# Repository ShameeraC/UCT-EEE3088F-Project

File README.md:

# EEE3088F Group 18 Sensing HAT (Version 1.0)
This project is a group project for the course EEE3088F at UCT. The purpose of the HAT is to detect light and move a motor or another device in the direction of the light.

# Instructions For Use (For Version 1.0)
    
    - Hardware Requirements - 

    To use this HAT, a mini-USB connector is required to interface the HAT with the STM 
    (Or whatever other microcontroller is in use). That being said, an STM32F0 discovery board, 
    or another board containing a microcontroller with read/write/ADC/memory capabilities must be used if 
    the full functionality of the HAT is to be claimed.
    The USB must be capable of data transmission.
    A 5V Li-Ion battery and battery holder are necessary for the powering of the HAT, unless some other 
    power source is to be used. Jumper cables are necessary for the current design, as it does not conform
    to the general standard of board measurements (they are needed to connect the HAT to the board in use).
   
    - Software Requirements -

    The coding of this board can be done via the STM Cube IDE (preferred) or Code Blocks. Other coding
    platforms can work as well. The terminal must be configured to drive the USB ports that connect to the
    discovery board or the HAT. 
    Programs can be uploaded to the STM or to the HAT itself, depending on which method is preferred.
    The EEPROM on the HAT must be coded via the HAT's USB port, as this sends data to and from the FTDI
    and the EEPROM on board the HAT together. 
    Currently the HAT has not been revised, and secondary versions have not yet been created. Because of this,
    the recommended approach to coding is to do so via the STM or the board in use (and not via the HAT).
    The temperature sensor which sends data to and from the HAT's EEPROM was not populated in version 1.0,
    and as such the EEPROM and the FTDI on board the HAT are not needed or useful currently.
    Thus, any code that is written should be uploaded directly to the board in use, after which wiring
    can interface the board with the HAT.

    - Initialization Instructions -

    To initialize the hardware, connect the battery to the HAT to power the STM board (if batteries 
    are not being used, find another way to connect the HAT to power). Connect each 
    pin on the STM to the corresponding pin on the HAT via jumper wires.
    To initialize the software, connect to the board via a USB, and compile and upload the desired 
    code to the board via an appropriate IDE. How to upload code to the board will vary from IDE to
    IDE. Check the IDE's online documentation for further details.

    - Running Your First Program on the HAT - 

    To run your first program on the HAT, refer to the self-explanatory code in the "main.c" file
    in the following directory:
    "Firmware/GROUP18 Microcontroler Interfacing/Core/src/main.c"
    This file can be run to toggle two user connected LEDs based on the strength of light sensed by
    the LDRs on the HAT. To set up the hardware for this basic program, two LEDs should be connected
    in series with 1k resistors which will be connected to GPIOA and GPIOB on the STM (GPIO pin 10 and
    pin 12 respectively). Alternitavely, the LEDs on the STM can be flashed based on the state of the
    LDRs if the STM LEDs are set to "HIGH" in the lightSensingInit() function (this would need to be
    added). Inside of the while loop in the code, the first statement is a call to initialize the light
    sensing sequence, and so everything is set up for ease of use.
    Have fun!! 

# Directories:
This repo has the following subfolders, which provide a useful common structure for custom electronics projects: \
    * Documentation: Project documentation (including submissions) and component datasheets are stored here.\
    * Firmware: Any software developed for the hat will be stored here.\
    * PCB: This includes all KiCad files (schematics, pcb, gerber files, footprints etc.). The main KiCad folder is here. \
    * Production: The gerber files, BOM, Budget, or anything required by JLCPCB will be stored here. \
    * Simulation: Any simulation files (eg SPICE) or design stage generated results (Eg matlab or excel) will be stored here.

# PCB Designers:
JONATHAN APPS \
SHAMEERA CASSIM \
JAHAR PERSAD 

# License
[Creative Commons Attribution 4.0 International license](https://choosealicense.com/licenses/cc-by-4.0/)

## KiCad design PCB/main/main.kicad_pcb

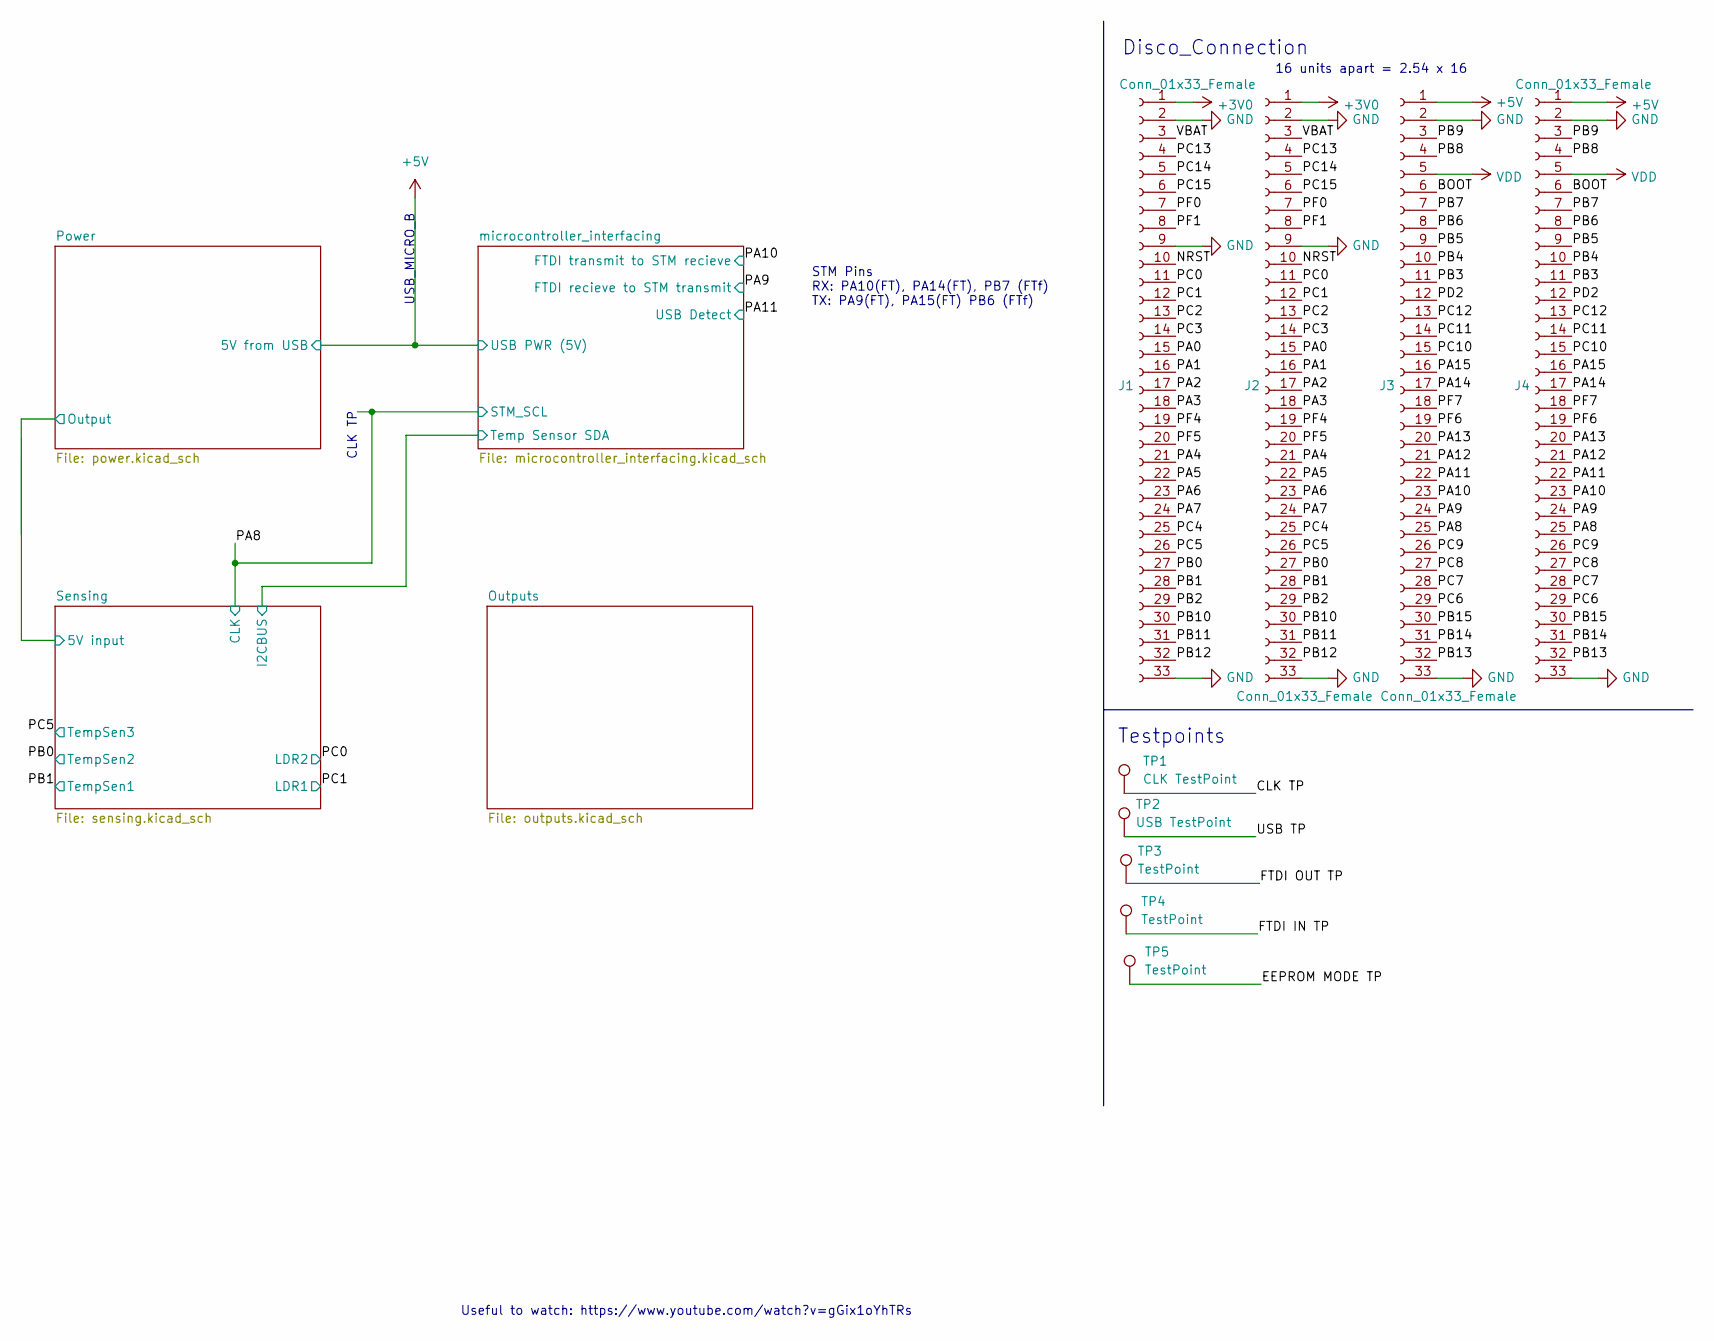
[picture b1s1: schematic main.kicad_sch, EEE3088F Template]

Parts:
J1, J4: Conn_01x33_Female; PinHeader_1x33_P2.54mm_Vertical
J2, J3: Conn_01x33_Female; PinSocket_1x33_P2.54mm_Vertical
TP1: CLK TestPoint; TestPoint_2Pads_Pitch2.54mm_Drill0.8mm
TP2: USB TestPoint; TestPoint_2Pads_Pitch2.54mm_Drill0.8mm
TP3, TP4, TP5: TestPoint; TestPoint_2Pads_Pitch2.54mm_Drill0.8mm

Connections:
+3V0: J1.1, J2.1
+5V: J3.1, J4.1; also elsewhere on the board
/BOOT: J3.6, J4.6
/NRST: J1.10, J2.10
/PA0: J1.15, J2.15
/PA1: J1.16, J2.16
/PA2: J1.17, J2.17
/PA3: J1.18, J2.18
/PA4: J1.21, J2.21
/PA5: J1.22, J2.22
/PA6: J1.23, J2.23
/PA7: J1.24, J2.24
/PA8: J3.25, J4.25; also elsewhere on the board
/PA9: J3.24, J4.24; also elsewhere on the board
/PA10: J3.23, J4.23; also elsewhere on the board
/PA11: J3.22, J4.22; also elsewhere on the board
/PA12: J3.21, J4.21
/PA13: J3.20, J4.20
/PA14: J3.17, J4.17
/PA15: J3.16, J4.16
/PB0: J1.27, J2.27; also elsewhere on the board
/PB1: J1.28, J2.28; also elsewhere on the board
/PB2: J1.29, J2.29
/PB3: J3.11, J4.11
/PB4: J3.10, J4.10
/PB5: J3.9, J4.9
/PB6: J3.8, J4.8
/PB7: J3.7, J4.7
/PB8: J3.4, J4.4
/PB9: J3.3, J4.3
/PB10: J1.30, J2.30
/PB11: J1.31, J2.31
/PB12: J1.32, J2.32
/PB13: J3.32, J4.32
/PB14: J3.31, J4.31
/PB15: J3.30, J4.30
/PC0: J1.11, J2.11; also elsewhere on the board
/PC1: J1.12, J2.12; also elsewhere on the board
/PC2: J1.13, J2.13
/PC3: J1.14, J2.14
/PC4: J1.25, J2.25
/PC5: J1.26, J2.26; also elsewhere on the board
/PC6: J3.29, J4.29
/PC7: J3.28, J4.28
/PC8: J3.27, J4.27
/PC9: J3.26, J4.26
/PC10: J3.15, J4.15
/PC11: J3.14, J4.14
/PC12: J3.13, J4.13
/PC13: J1.4, J2.4
/PC14: J1.5, J2.5
/PC15: J1.6, J2.6
/PD2: J3.12, J4.12
/PF0: J1.7, J2.7
/PF1: J1.8, J2.8
/PF4: J1.19, J2.19
/PF5: J1.20, J2.20
/PF6: J3.19, J4.19
/PF7: J3.18, J4.18
/VBAT: J1.3, J2.3
GND: J1.2, J1.9, J1.33, J2.2, J2.9, J2.33, J3.2, J3.33, J4.2, J4.33; also elsewhere on the board
VDD: J3.5, J4.5

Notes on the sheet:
Useful to watch: https://www.youtube.com/watch?v=gGix1oYhTRs
CLK TP
STM Pins RX: PA10(FT), PA14(FT), PB7 (FTf) TX: PA9(FT), PA15(FT) PB6 (FTf)
USB_MICRO_B
16 units apart = 2.54 x 16
Disco_Connection
Testpoints

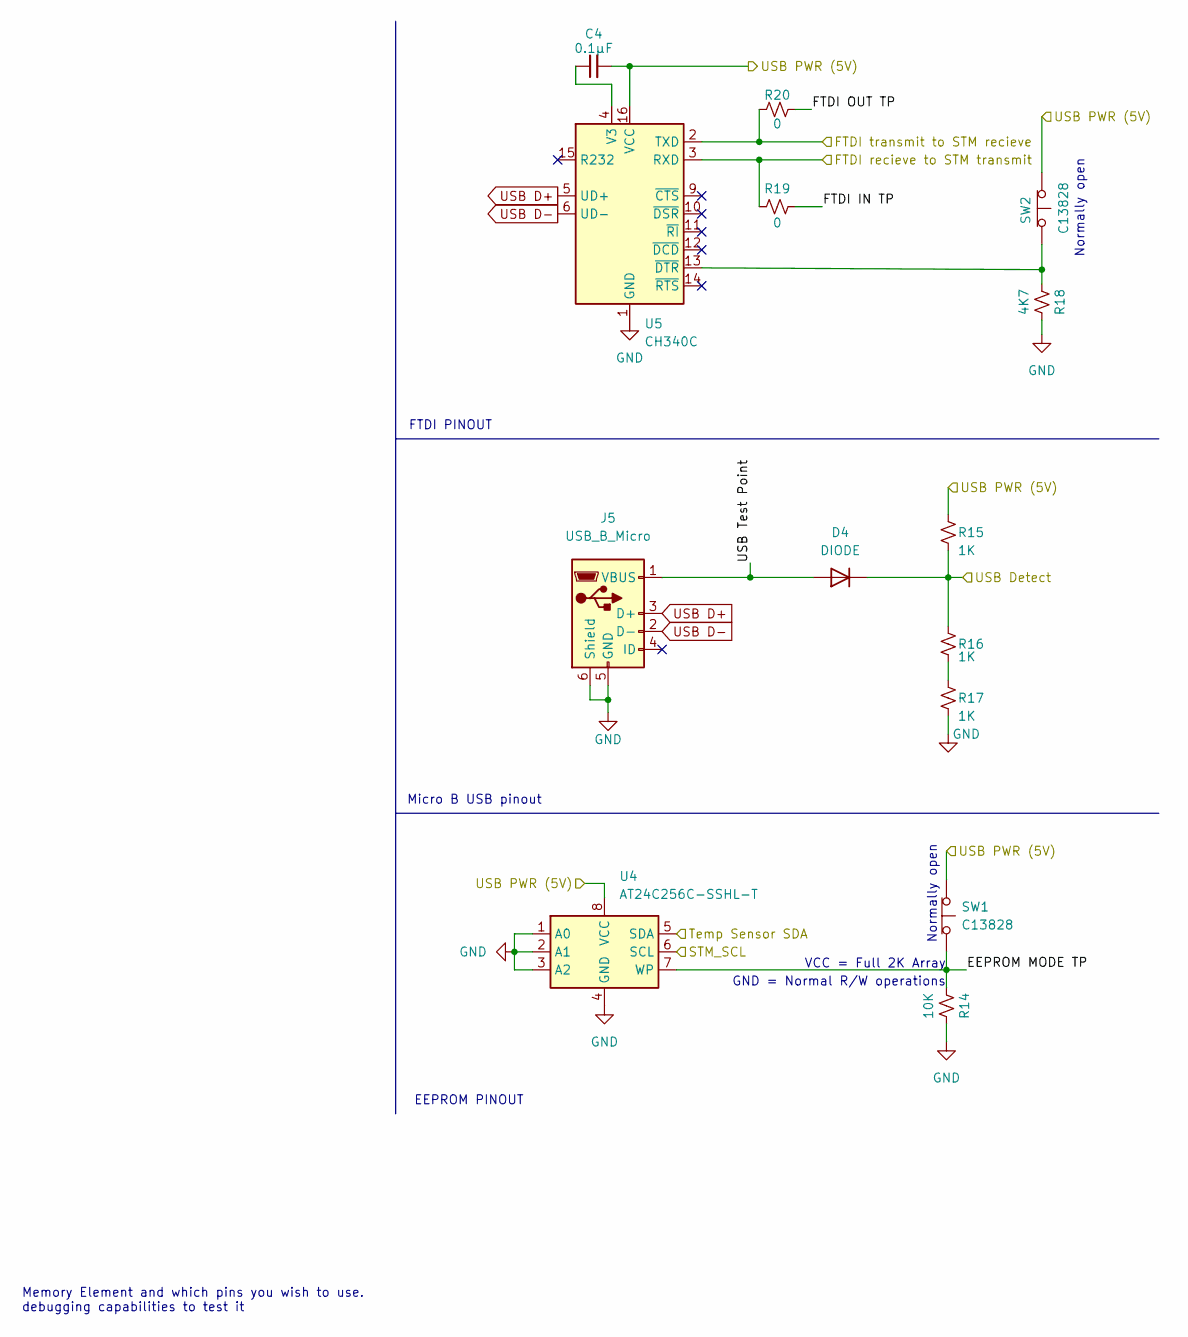
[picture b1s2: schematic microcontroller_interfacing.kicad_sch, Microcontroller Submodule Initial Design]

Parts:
C4: 0.1μF; C_0201_0603Metric; LCSC C141382
D4: DIODE; LED_0805_2012Metric; LCSC C2480
J5: USB_B_Micro; USB_Micro-B_Amphenol_10103594-0001LF_Horizontal; LCSC C404969
R14: 10K; R_0603_1608Metric; LCSC C25804
R15, R16, R17: 1K; R_0603_1608Metric; LCSC C21190
R18: 4K7; R_0603_1608Metric; LCSC C23162
R19, R20: 0; R_0603_1608Metric; LCSC C21189
SW1, SW2: C13828; SW_1825910-6-4; LCSC C13828
U4: AT24C256C-SSHL-T; EEPROM; LCSC C6482
U5: CH340C; SOP-16_3.9x9.9mm_P1.27mm; LCSC C84681

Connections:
+5V: C4.2, R15.1, SW1.1 (A), SW2.1 (A), U4.8 (VCC), U5.16 (VCC); also elsewhere on the board
/PA8: U4.6 (SCL); also elsewhere on the board
/PA9: R19.1, U5.3 (RXD); also elsewhere on the board
/PA10: R20.1, U5.2 (TXD); also elsewhere on the board
/PA11: D4.2 (K), R15.2, R16.1; also elsewhere on the board
/Sensing/I2CBUS: U4.5 (SDA); also elsewhere on the board
/microcontroller_interfacing/EEPROM MODE TP: R14.1, SW1.2 (B), U4.7 (WP)
/microcontroller_interfacing/FTDI IN TP: R19.2
/microcontroller_interfacing/FTDI OUT TP: R20.2
/microcontroller_interfacing/USB Test Point: D4.1 (A), J5.1 (VBUS)
GND: J5.5 (GND), J5.6 (Shield), R14.2, R17.2, R18.2, U4.1 (A0), U4.2 (A1), U4.3 (A2), U4.4 (GND), U5.1 (GND); also elsewhere on the board
unnamed: C4.1, U5.4 (V3)
unnamed: R16.2, R17.1
unnamed: R18.1, SW2.2 (B), U5.13 (~DTR)
USB D+: J5.3 (D+), U5.5 (UD+)
USB D-: J5.2 (D-), U5.6 (UD-)

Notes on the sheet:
EEPROM PINOUT
VCC = Full 2K Array
Micro B USB pinout
Normally open
Memory Element and which pins you wish to use. debugging capabilities to test it
GND = Normal R/W operations
FTDI PINOUT

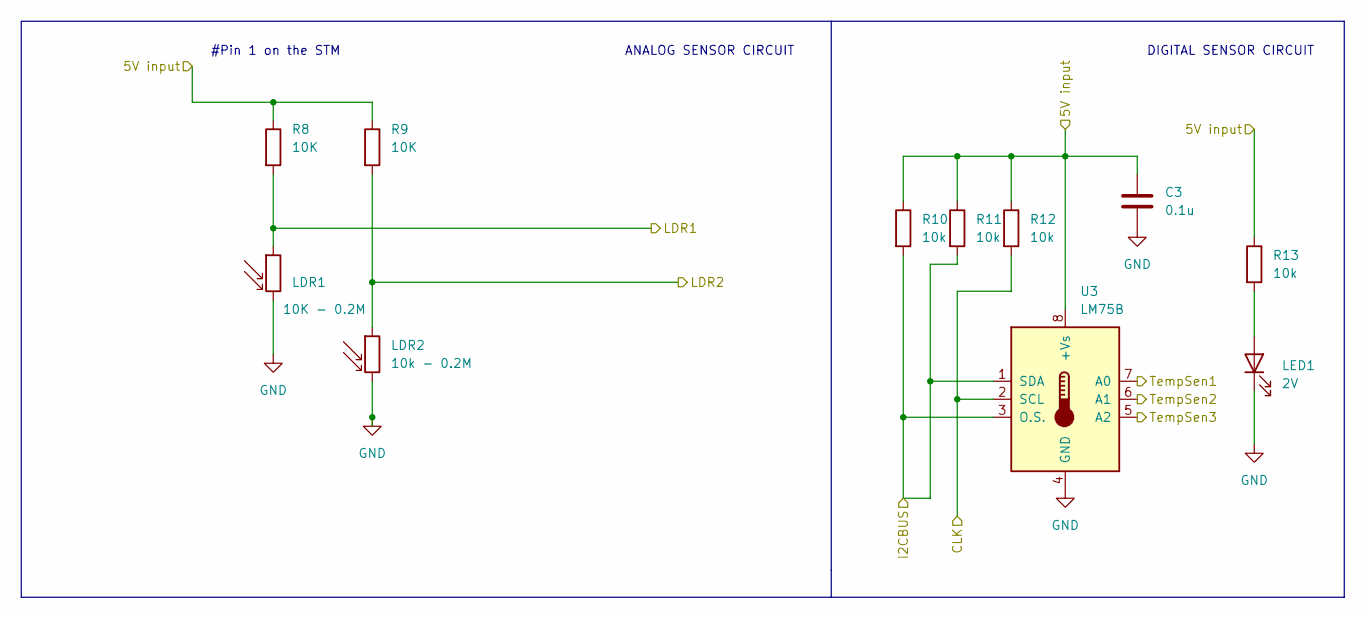
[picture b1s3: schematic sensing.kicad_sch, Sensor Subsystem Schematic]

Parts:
C3: 0.1u; C_0201_0603Metric; LCSC C141382
LDR1: 10K - 0.2M; R_Axial_DIN0204_L3.6mm_D1.6mm_P1.90mm_Vertical; LCSC C779572
LDR2: 10k - 0.2M; R_Axial_DIN0204_L3.6mm_D1.6mm_P1.90mm_Vertical; LCSC C779572
LED1: 2V; LED_0805_2012Metric; LCSC C84256
R8, R9: 10K; R_0603_1608Metric; LCSC C25804
R10, R11, R12, R13: 10k; R_0603_1608Metric; LCSC C25804
U3: LM75B; SOIC127P600X175-8N; LCSC C34565

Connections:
/PA8: R12.2, U3.2 (SCL); also elsewhere on the board
/PB0: U3.6 (A1); also elsewhere on the board
/PB1: U3.7 (A0); also elsewhere on the board
/PC0: LDR2.1, R9.2; also elsewhere on the board
/PC1: LDR1.1, R8.2; also elsewhere on the board
/PC5: U3.5 (A2); also elsewhere on the board
/Power/Output: C3.1, R8.1, R9.1, R10.1, R11.1, R12.1, R13.1, U3.8 (+Vs); also elsewhere on the board
/Sensing/I2CBUS: R10.2, R11.2, U3.1 (SDA), U3.3 (O.S.); also elsewhere on the board
GND: C3.2, LDR1.2, LDR2.2, LED1.1 (K), U3.4 (GND); also elsewhere on the board
unnamed: LED1.2 (A), R13.2

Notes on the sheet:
DIGITAL SENSOR CIRCUIT
#Pin 1 on the STM
ANALOG SENSOR CIRCUIT

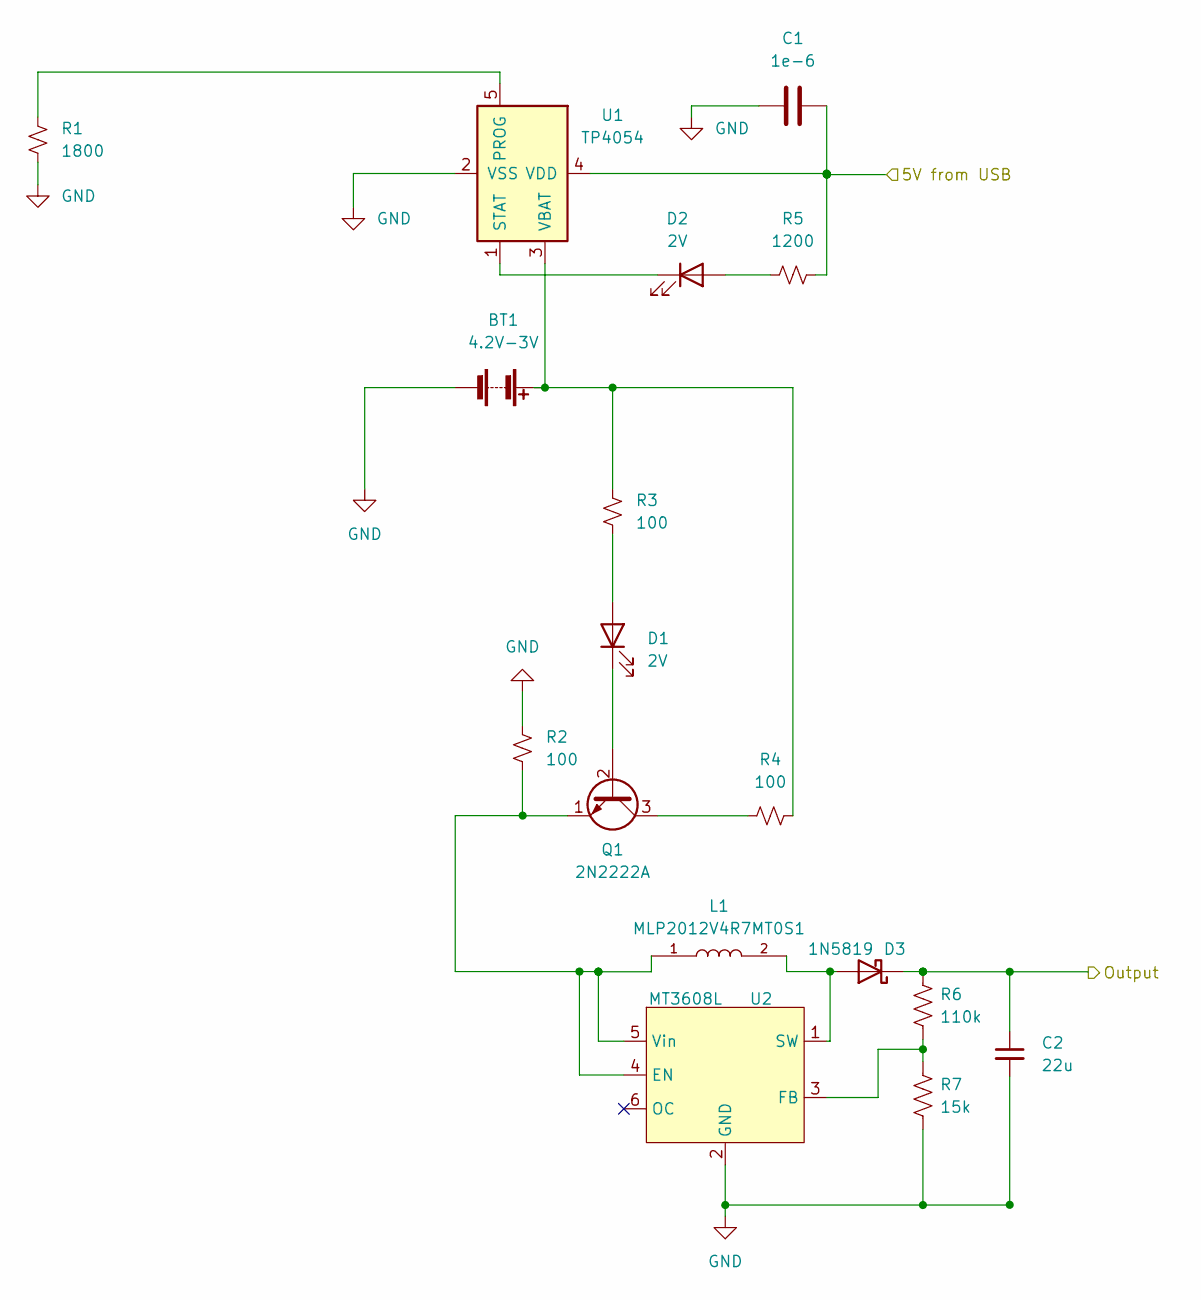
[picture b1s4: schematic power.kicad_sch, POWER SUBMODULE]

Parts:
BT1: 4.2V-3V; BatteryHolder_Keystone_1042_1x18650
C1: 1e-6; C_0201_0603Metric; LCSC C15849
C2: 22u; C_0805_2012Metric; LCSC C45783
D1, D2: 2V; LED_0805_2012Metric; LCSC C84256
D3: 1N5819; D_SOD-323; LCSC C191023
L1: MLP2012V4R7MT0S1; INDC2012X87N; LCSC C383376
Q1: 2N2222A; TO-92; LCSC C118536
R1: 1800; R_0201_0603Metric; LCSC C4177
R2, R3, R4: 100; R_0201_0603Metric; LCSC C22775
R5: 1200; R_0201_0603Metric; LCSC C22765
R6: 110k; R_0201_0603Metric; LCSC C25805
R7: 15k; R_0201_0603Metric; LCSC C22809
U1: TP4054; SOT-23-5; LCSC C32574
U2: MT3608L; SOT-23-6; LCSC C2932326

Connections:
/Power/Output: C2.1, D3.1 (K), R6.1; also elsewhere on the board
GND: BT1.2 (-), C1.2, C2.2, R1.2, R2.1, R7.2, U1.2 (VSS), U2.2 (GND); also elsewhere on the board
unnamed: BT1.1 (+), R3.1, R4.2, U1.3 (VBAT)
unnamed: C1.1, R5.2, U1.4 (VDD)
unnamed: D1.1 (K), Q1.2 (B)
unnamed: D1.2 (A), R3.2
unnamed: D2.1 (K), U1.1 (STAT)
unnamed: D2.2 (A), R5.1
unnamed: D3.2 (A), L1.2, U2.1 (SW)
unnamed: L1.1, U2.4 (EN), U2.5 (Vin)
unnamed: Q1.1 (E), R2.2
unnamed: Q1.3 (C), R4.1
unnamed: R1.1, U1.5 (PROG)
unnamed: R6.2, R7.1, U2.3 (FB)

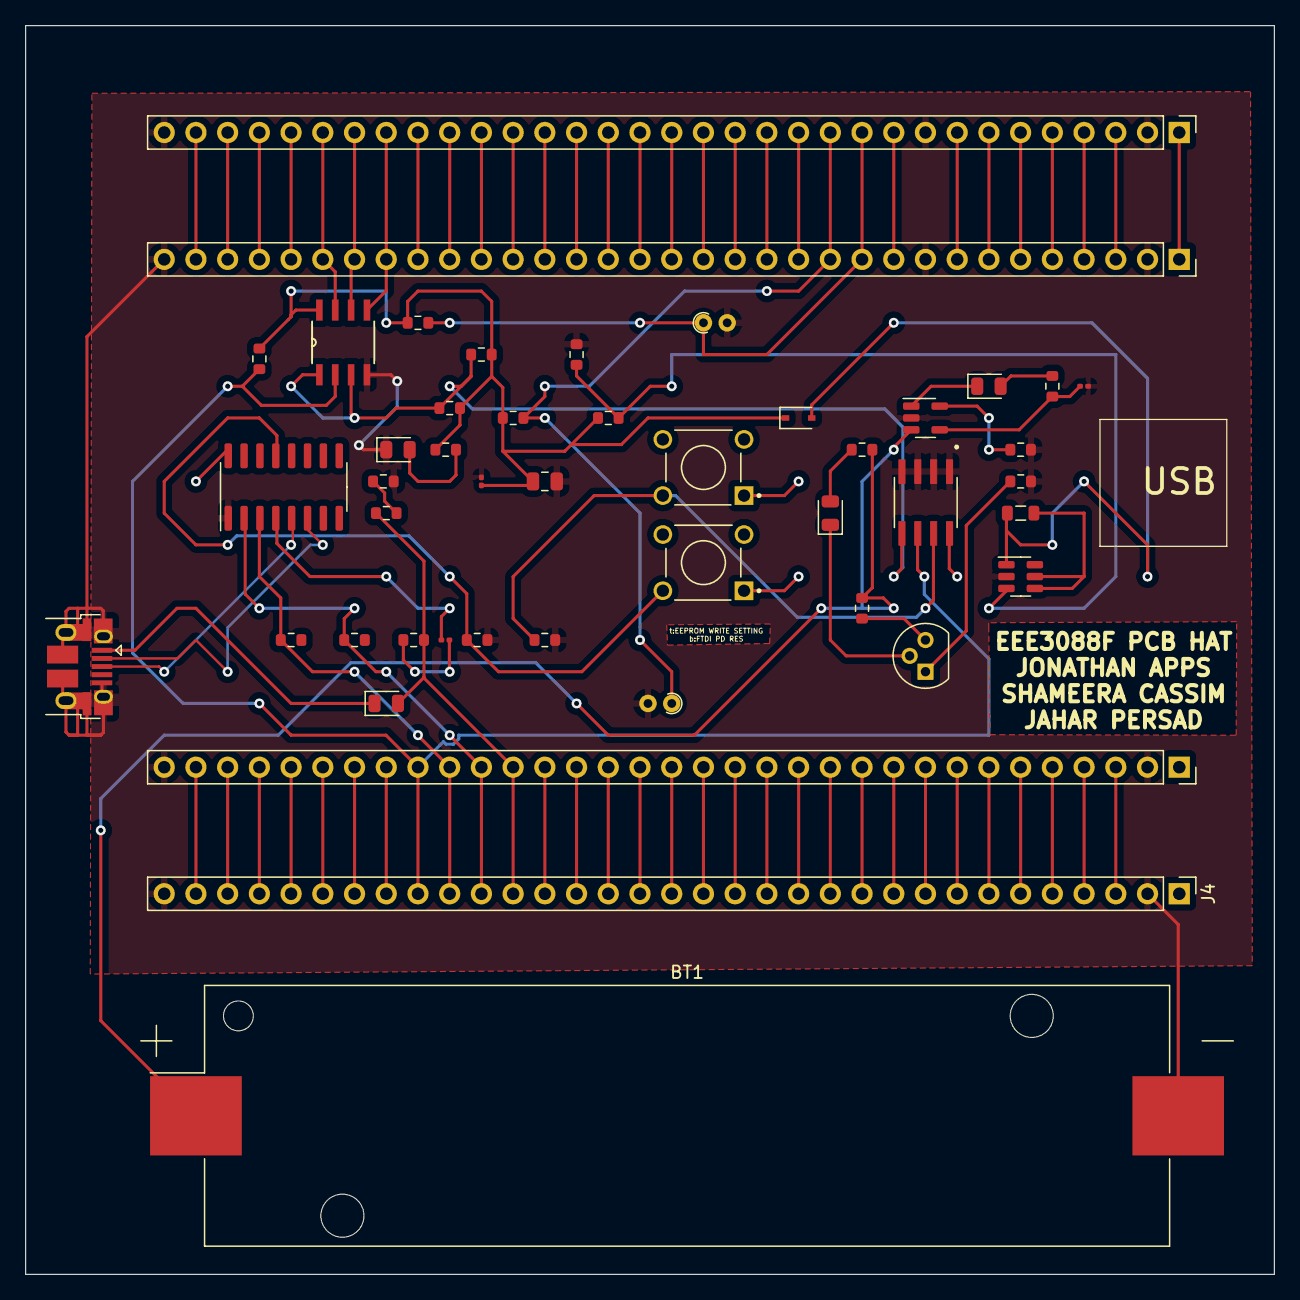
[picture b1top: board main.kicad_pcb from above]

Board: 2 copper layers, 100.0 x 100.0 mm, 46 parts (0 on the bottom side), 84 nets.

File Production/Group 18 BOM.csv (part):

"Source:","C:\Users\USER\Desktop\eee3088f-group-18-project\PCB\main\main.kicad_sch"
"Date:","2022/04/08 18:45:28"
"Tool:","Eeschema (6.0.2)"
"Generator:","C:\Program Files\KiCad\6.0\bin\scripting\plugins/bom_csv_grouped_by_value.py"
"Component Count:","51"

"Individual Components:"

"Item","Qty","Reference(s)","Value","LibPart","Footprint","Datasheet","LCSC","Populate","Price","Spice_Netlist_Enabled","Spice_Primitive"
"","","BT1","4.2V-3V","Device:Battery","Battery:BatteryHolder_Keystone_1042_1x18650","~","","DNP","","",""
"","","C1","1e-6","Device:C","Capacitor_SMD:C_0201_0603Metric","~","C15849","P","0.0055","",""
"","","C2","22u","Device:C_Small","Capacitor_SMD:C_0805_2012Metric","https://datasheet.lcsc.com/lcsc/1811151152_Samsung-Electro-M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","C45783","P","0.0361","",""
"","","C3","0.1u","Device:C","Capacitor_SMD:C_0201_0603Metric","~","C141382","P","0.0032","",""
"","","C4","0.1μF","Device:C_Small","Capacitor_SMD:C_0201_0603Metric","https://datasheet.lcsc.com/lcsc/1809291616_TORCH-CT41-0603-2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","C141382","P","0.0032","",""
"","","D1","2V","Device:LED","LED_SMD:LED_0805_2012Metric","~https://datasheet.lcsc.com/lcsc/2008201032_Foshan-NationStar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","C84256","P","0.0136","",""
"","","D2","2V","Device:LED","LED_SMD:LED_0805_2012Metric","~","C84256","P","0.0136","",""
"","","D3","1N5819","Diode:1N5819","Diode_SMD:D_SOD-323","https://datasheet.lcsc.com/lcsc/1810202112_Guangdong-Hottech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","C191023","P","0.0279","",""
"","","D4","DIODE","Simulation_SPICE:DIODE","LED_SMD:LED_0805_2012Metric","https://datasheet.lcsc.com/lcsc/2105061432_MDD-Microdiode-El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","C2480","P","0.0179","Y","D"
"","","EEPROM1","AT24C256C-SSHL-T","Memory_EEPROM:CAT24C256","SOIC127P600X175-8N:EEPROM","https://www.onsemi.cn/PowerSolutions/document/CAT24C256-D.PDF","C6482","P","1.4287","",""
"","","FTDI(UART)1","CH340C","Interface_USB:CH340C","CH340C:SOIC127P600X180-16N","https://datasheet.lcsc.com/szlcsc/Jiangsu-Qin-Heng-CH340C_C8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","C84681","P","0.5589","Center","Center"
"","","J1","Conn_01x33_Female","Connector:Conn_01x33_Female","Connector_PinHeader_2.54mm:PinHeader_1x33_P2.54mm_Vertical","~","","DNP","0","",""
"","","J2","Conn_01x33_Female","Connector:Conn_01x33_Female","Connector_PinSocket_2.54mm:PinSocket_1x33_P2.54mm_Vertical","~","","DNP","0","",""
"","","J3","Conn_01x33_Female","Connector:Conn_01x33_Female","Connector_PinSocket_2.54mm:PinSocket_1x33_P2.54mm_Vertical","~","","DNP","0","",""
"","","J4","Conn_01x33_Female","Connector:Conn_01x33_Female","Connector_PinHeader_2.54mm:PinHeader_1x33_P2.54mm_Vertical","~","","DNP","0","",""
"","","J5","USB_B_Micro","Connector:USB_B_Micro","Connector_USB:USB_Micro-B_Amphenol_10103594-0001LF_Horizontal","~","C404969","P","0.047","",""
"","","L1","MLP2012V4R7MT0S1","Custom:MLP2012V4R7MT0S1","3088HAT:INDC2012X87N","https://datasheet.lcsc.com/lcsc/1912111437_TDK-MLP2012V4R7MT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","C383376","P","0.0425","",""
"","","LDR1","10K - 0.2M","Device:R_Photo","Resistor_SMD:R_0201_0603Metric","~","C779572","P","0.0503","",""
"","","LDR2","10k - 0.2M","Device:R_Photo","Resistor_SMD:R_0201_0603Metric","~","C779572","P","0.0503","",""
"","","LED1","2V","Device:LED","LED_SMD:LED_0805_2012Metric","~","C84256","P","0.0136","",""
"","","Q1","2N2222A","Transistor_BJT:2N2219","Package_TO_SOT_THT:TO-92","http://www.onsemi.com/pub_link/Collateral/2N2219-D.PDF","C118536","P","0.0214","",""
"","","R1","1800","Device:R_Small_US","Resistor_SMD:R_0201_0603Metric","~","C4177","P","0.0013","",""
"","","R2","100ohms","Device:R_Small_US","Resistor_SMD:R_0201_0603Metric","~","C22775","P","0.0012","",""
"","","R3","100ohms","Device:R_Small_US","Resistor_SMD:R_0201_0603Metric","~","C22775","P","0.0012","",""
"","","R4","100ohms","Device:R_Small_US","Resistor_SMD:R_0201_0603Metric","~","C22775","P","0.0012","",""
"","","R5","1200","Device:R_Small_US","Resistor_SMD:R_0201_0603Metric","~","C22765","P","0.0013","",""
"","","R6","110k","Device:R_US","Resistor_SMD:R_0201_0603Metric","https://datasheet.lcsc.com/lcsc/2110260030_UNI-ROYAL-Uniroya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","C25805","P","0.0014","",""
"","","R7","15k","Device:R_US","Resistor_SMD:R_0201_0603Metric","https://datasheet.lcsc.com/lcsc/2110252030_UNI-ROYAL-Uniroya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","C22809","P","0.0013","",""
"","","R8","10K","Device:R","Resistor_SMD:R_0201_0603Metric","https://datasheet.lcsc.com/lcsc/2110260030_UNI-ROYAL-Uniroya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","C25804","P","0.0012","",""
"","","R9","10K","Device:R","Resistor_SMD:R_0201_0603Metric","https://datasheet.lcsc.com/lcsc/2110260030_UNI-ROYAL-Uniroya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","C25804","P","0.0012","",""
"","","R10","10k","Device:R","Resistor_SMD:R_0201_0603Metric","https://datasheet.lcsc.com/lcsc/2110260030_UNI-ROYAL-Uniroya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","C25804","P","0.0012","",""
"","","R11","10k","Device:R","Resistor_SMD:R_0201_0603Metric","https://datasheet.lcsc.com/lcsc/2110260030_UNI-ROYAL-Uniroya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","C25804","P","0.0012","",""
"","","R12","10k","Device:R","Resistor_SMD:R_0201_0603Metric","https://datasheet.lcsc.com/lcsc/2110260030_UNI-ROYAL-Uniroya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","C25804","P","0.0012","",""
"","","R13","10k","Device:R","Resistor_SMD:R_0201_0603Metric","https://datasheet.lcsc.com/lcsc/2110260030_UNI-ROYAL-Uniroya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","C25804","P","0.0012","",""
"","","R14","10K","Device:R_Small_US","Resistor_SMD:R_0201_0603Metric","https://datasheet.lcsc.com/lcsc/2110260030_UNI-ROYAL-Uniroya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","C25804","P","0.0012","",""
"","","R15","1K","Device:R_Small_US","Resistor_SMD:R_0201_0603Metric","https://datasheet.lcsc.com/lcsc/2110252030_UNI-ROYAL-Uniroya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","C21190","P","0.0012","",""
"","","R16","1K","Device:R_Small_US","Resistor_SMD:R_0201_0603Metric","https://datasheet.lcsc.com/lcsc/2110252030_UNI-ROYAL-Uniroya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","C21190","P","0.0012","",""
"","","R17","1K","Device:R_Small_US","Resistor_SMD:R_0201_0603Metric","https://datasheet.lcsc.com/lcsc/2110252030_UNI-ROYAL-Uniroya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","C21190","P","0.0012","",""
"","","R18","4K7","Device:R_Small_US","Resistor_SMD:R_0201_0603Metric","https://datasheet.lcsc.com/lcsc/2110252130_UNI-ROYAL-Uniroya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","C23162","P","0.0012","",""
"","","R19","0","Device:R_Small_US","Resistor_SMD:R_0201_0603Metric","https://datasheet.lcsc.com/lcsc/2110252030_UNI-ROYAL-Uniroya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","C21189","P","0.0012","",""
"","","R20","0","Device:R_Small_US","Resistor_SMD:R_0201_0603Metric","https://datasheet.lcsc.com/lcsc/2110252030_UNI-ROYAL-Uniroya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","C21189","P","0.0012","",""
"","","SW1","C13828","Switch:SW_Push_Open","1825910-6:SW_1825910-6-4","https://datasheet.lcsc.com/szlcsc/1912111437_Dongguan-Guangz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","C13828","P","0.0394","",""
"","","SW2","C13828","Switch:SW_Push_Open","1825910-6:SW_1825910-6-4","https://datasheet.lcsc.com/szlcsc/1912111437_Dongguan-Guangz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","C13828","P","0.0394","",""
"","","TempSensor1","LM75B","Sensor_Temperature:LM75B","LM75BD:SOIC127P600X175-8N","http://www.ti.com/lit/ds/symlink/lm75b.pdf","C2837470","P","0.4002","",""
"","","TP1","CLK TestPoint","Connector:TestPoint","TestPoint:TestPoint_2Pads_Pitch2.54mm_Drill0.8mm","~","","DNP","","",""
"","","TP2","USB TestPoint","Connector:TestPoint","TestPoint:TestPoint_2Pads_Pitch2.54mm_Drill0.8mm","~","","DNP","","",""
"","","TP3","TestPoint","Connector:TestPoint","TestPoint:TestPoint_2Pads_Pitch2.54mm_Drill0.8mm","~","","DNP","","",""
"","","TP4","TestPoint","Connector:TestPoint","TestPoint:TestPoint_2Pads_Pitch2.54mm_Drill0.8mm","~","","DNP","","",""
"","","TP5","TestPoint","Connector:TestPoint","TestPoint:TestPoint_2Pads_Pitch2.54mm_Drill0.8mm","~","","DNP","","",""
"","","U1","TP4054","Battery_Management:MCP73831-2-OT","Package_TO_SOT_SMD:SOT-23-5","http://ww1.microchip.com/downloads/en/DeviceDoc/20001984g.pdf","C32574","P","0.1555","",""
"","","U2","MT3608L","Custom:MT3608L","Package_TO_SOT_SMD:SOT-23-6","https://datasheet.lcsc.com/lcsc/2201121530_XI-AN-Aerosemi-Te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","C2932326","P","0.0693","",""



"Collated Components:"

"Item","Qty","Reference(s)","Value","LibPart","Footprint","Datasheet","LCSC","Populate","Price","Spice_Netlist_Enabled","Spice_Primitive"
"1","1","BT1","4.2V-3V","Device:Battery","Battery:BatteryHolder_Keystone_1042_1x18650","~","","DNP","","",""
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
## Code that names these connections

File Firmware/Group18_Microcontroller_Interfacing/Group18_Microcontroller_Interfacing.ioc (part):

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Mcu.Name=STM32F051R8Tx
Mcu.Package=LQFP64
Mcu.UserName=STM32F051R8Tx
PA10.Mode=Asynchronous
PA10.Signal=USART1_RX
PA8.Signal=GPIO_Output
PA9.Mode=Asynchronous
PA9.Signal=USART1_TX
PB0.Mode=IN8
PB0.Signal=ADC_IN8
PB1.Mode=IN9
PB1.Signal=ADC_IN9
PB10.Mode=I2C
PB10.Signal=I2C2_SCL
PB11.Mode=I2C
PB11.Signal=I2C2_SDA
PC0.Mode=IN10
PC0.Signal=ADC_IN10
PC1.Mode=IN11
PC1.Signal=ADC_IN11
PC5.Mode=IN15
PC5.Signal=ADC_IN15
board=custom

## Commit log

2022-04-04 Submission PDFs, Datasheets and any other relevant documentation included here
2022-04-04 All kiCad files to be stored here
2022-04-04 All files necessary for production included here
2022-04-04 Software for HAT to be stored here
2022-04-04 Simulation files to be stored here
2022-04-04 All updated schematics, gerbers and error checking reports from old git organized and added
2022-04-04 updated microcontroller schematic and added documentation
2022-04-04 Week 5 BOMs added to documentation
2022-04-05 new power module
2022-04-05 Replace main.kicad_pcb
2022-04-05 Replace sensing.kicad_sch
2022-04-05 Replace power.kicad_sch
2022-04-05 Replace outputs.kicad_sch
2022-04-05 Replace microcontroller_interfacing.kicad_sch
2022-04-05 Replace main.net
2022-04-05 Replace main.kicad_sch
2022-04-05 Replace main.kicad_pro
2022-04-05 Replace main.kicad_prl
2022-04-05 Replace fp-info-cache
2022-04-05 updated microcontroller submodule
2022-04-08 Replace main.kicad_pcb - FINALLLLLLLLL
2022-04-08 updated gerbers and finalized PCB
2022-04-08 gerbers, BOM and CPL(pos) files added
2022-04-08 finalized gerbers and fabrication files
2022-04-12 Footprint folder updated
2022-04-12 added new jlcpcb files. other group members to double check
2022-04-13 updated PCB & Assembly file
2022-04-14 Updated PCB
2022-04-14 Updated schematic (correct footprints)
2022-04-14 rewired PCB and changed relevant footprints. production files regenerated
2022-04-22 translated datasheet added
2022-05-19 Configuration and FTDI test code
2022-05-21 EEPROM and UART code
2022-05-21 Replace main.c
2022-05-21 Documentation folder reorganized and code reference document uploaded
2022-05-21 updates to read and write to I2C functions
2022-05-21 spelling error ron folder name corrected
2022-05-22 Upload New File
2022-05-27 weekly submissions added
